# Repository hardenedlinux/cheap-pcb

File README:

## Cheap PCB: Better understanding the current status of hardware supply chain

We did this experimental for fun and profit( better assessment for hardware supply chain security). Read the [full story](https://github.com/hardenedlinux/cheap-pcb/blob/main/cheap-pcb-story.md).

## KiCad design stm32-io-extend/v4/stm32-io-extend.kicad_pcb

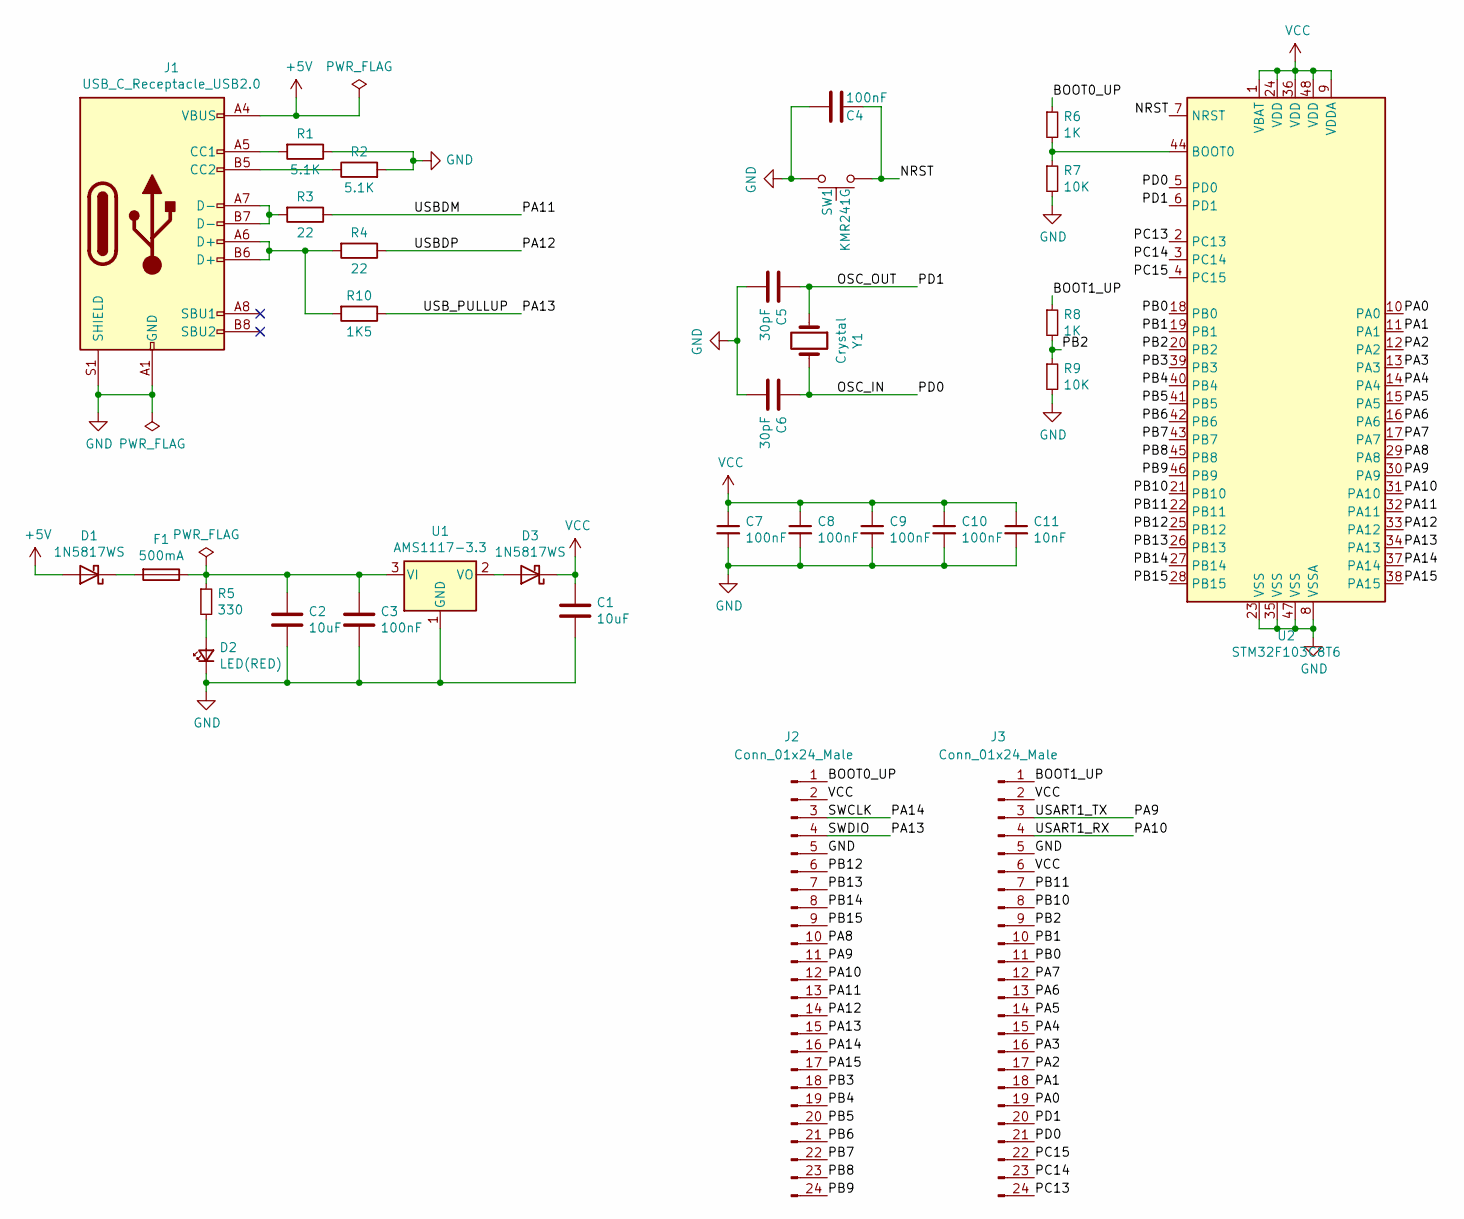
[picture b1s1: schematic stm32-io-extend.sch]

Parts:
C1, C2: 10uF; C_0603_1608Metric_Pad1.08x0.95mm_HandSolder
C3, C4, C7, C8, C9, C10: 100nF; C_0603_1608Metric_Pad1.08x0.95mm_HandSolder
C5, C6: 30pF; C_0603_1608Metric_Pad1.08x0.95mm_HandSolder
C11: 10nF; C_0603_1608Metric_Pad1.08x0.95mm_HandSolder
D1, D3: 1N5817WS; D_SOD-323_HandSoldering
D2: LED(RED); LED_0603_1608Metric_Pad1.05x0.95mm_HandSolder
F1: 500mA; Fuse_0805_2012Metric_Pad1.15x1.40mm_HandSolder
J1: USB_C_Receptacle_USB2.0; USB_C_Receptacle_Palconn_UTC16-G
J2, J3: Conn_01x24_Male; PinHeader_1x24_P2.54mm_Vertical
R1, R2: 5.1K; R_0603_1608Metric_Pad0.98x0.95mm_HandSolder
R3, R4: 22; R_0603_1608Metric_Pad0.98x0.95mm_HandSolder
R5: 330; R_0603_1608Metric_Pad0.98x0.95mm_HandSolder
R6, R8: 1K; R_0603_1608Metric_Pad0.98x0.95mm_HandSolder
R7, R9: 10K; R_0603_1608Metric_Pad0.98x0.95mm_HandSolder
R10: 1K5; R_0603_1608Metric_Pad0.98x0.95mm_HandSolder
SW1: KMR241G; SW_Push_1P1T-SH_NO_CK_KMR2xxG
U1: AMS1117-3.3; SOT-89-3_Handsoldering
U2: STM32F103C8T6; LQFP-48_7x7mm_P0.5mm
Y1: Crystal; Crystal_SMD_HC49-SD_HandSoldering

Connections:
+5V: D1.2 (A), J1.A4 (VBUS), J1.A9 (VBUS), J1.B4 (VBUS), J1.B9 (VBUS)
/BOOT0_UP: J2.1, R6.1
/BOOT1_UP: J3.1, R8.1
/NRST: C4.1, SW1.1, U2.7 (NRST)
/OSC_IN: C6.1, J3.21, U2.5 (PD0), Y1.2
/OSC_OUT: C5.1, J3.20, U2.6 (PD1), Y1.1
/PA0: J3.19, U2.10 (PA0)
/PA1: J3.18, U2.11 (PA1)
/PA2: J3.17, U2.12 (PA2)
/PA3: J3.16, U2.13 (PA3)
/PA4: J3.15, U2.14 (PA4)
/PA5: J3.14, U2.15 (PA5)
/PA6: J3.13, U2.16 (PA6)
/PA7: J3.12, U2.17 (PA7)
/PA8: J2.10, U2.29 (PA8)
/PA9: J2.11, J3.3, U2.30 (PA9)
/PA10: J2.12, J3.4, U2.31 (PA10)
/PA11: J2.13, R3.1, U2.32 (PA11)
/PA12: J2.14, R4.1, U2.33 (PA12)
/PA13: J2.4, J2.15, R10.1, U2.34 (PA13)
/PA14: J2.3, J2.16, U2.37 (PA14)
/PA15: J2.17, U2.38 (PA15)
/PB0: J3.11, U2.18 (PB0)
/PB1: J3.10, U2.19 (PB1)
/PB2: J3.9, R8.2, R9.1, U2.20 (PB2)
/PB3: J2.18, U2.39 (PB3)
/PB4: J2.19, U2.40 (PB4)
/PB5: J2.20, U2.41 (PB5)
/PB6: J2.21, U2.42 (PB6)
/PB7: J2.22, U2.43 (PB7)
/PB8: J2.23, U2.45 (PB8)
/PB9: J2.24, U2.46 (PB9)
/PB10: J3.8, U2.21 (PB10)
/PB11: J3.7, U2.22 (PB11)
/PB12: J2.6, U2.25 (PB12)
/PB13: J2.7, U2.26 (PB13)
/PB14: J2.8, U2.27 (PB14)
/PB15: J2.9, U2.28 (PB15)
/PC13: J3.24, U2.2 (PC13)
/PC14: J3.23, U2.3 (PC14)
/PC15: J3.22, U2.4 (PC15)
GND: C1.2, C2.2, C3.2, C4.2, C5.2, C6.2, C7.2, C8.2, C9.2, C10.2, C11.2, D2.1 (K), J1.A1 (GND), J1.A12 (GND), J1.B1 (GND), J1.B12 (GND), J1.S1 (SHIELD), J2.5, J3.5, R1.1, R2.2, R7.2, R9.2, SW1.2, U1.1 (GND), U2.8 (VSSA), U2.23 (VSS), U2.35 (VSS), U2.47 (VSS)
unnamed: C2.1, C3.1, F1.1, R5.1, U1.3 (VI)
unnamed: D1.1 (K), F1.2
unnamed: D2.2 (A), R5.2
unnamed: D3.2 (A), U1.2 (VO)
unnamed: J1.A5 (CC1), R1.2
unnamed: J1.A6 (D+), J1.B6 (D+), R4.2, R10.2
unnamed: J1.A7 (D-), J1.B7 (D-), R3.2
unnamed: J1.B5 (CC2), R2.1
unnamed: R6.2, R7.1, U2.44 (BOOT0)
VCC: C1.1, C7.1, C8.1, C9.1, C10.1, C11.1, D3.1 (K), J2.2, J3.2, J3.6, U2.1 (VBAT), U2.9 (VDDA), U2.24 (VDD), U2.36 (VDD), U2.48 (VDD)

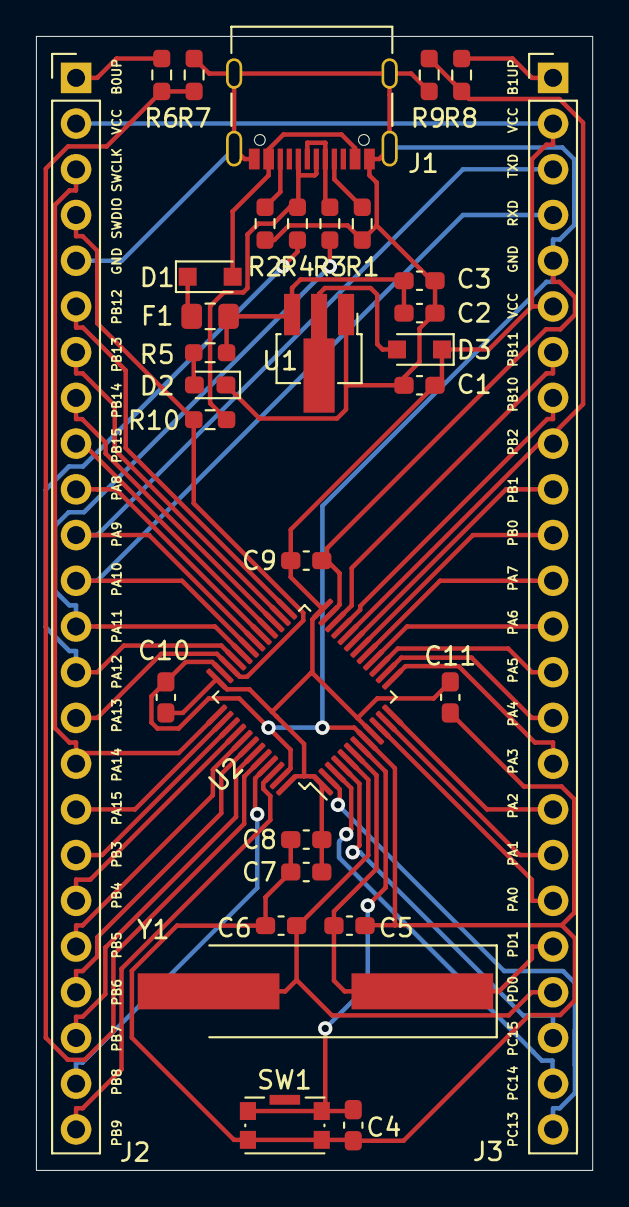
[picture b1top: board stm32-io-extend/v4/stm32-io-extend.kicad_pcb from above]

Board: 2 copper layers, 30.9 x 63.0 mm, 32 parts (0 on the bottom side), 52 nets.

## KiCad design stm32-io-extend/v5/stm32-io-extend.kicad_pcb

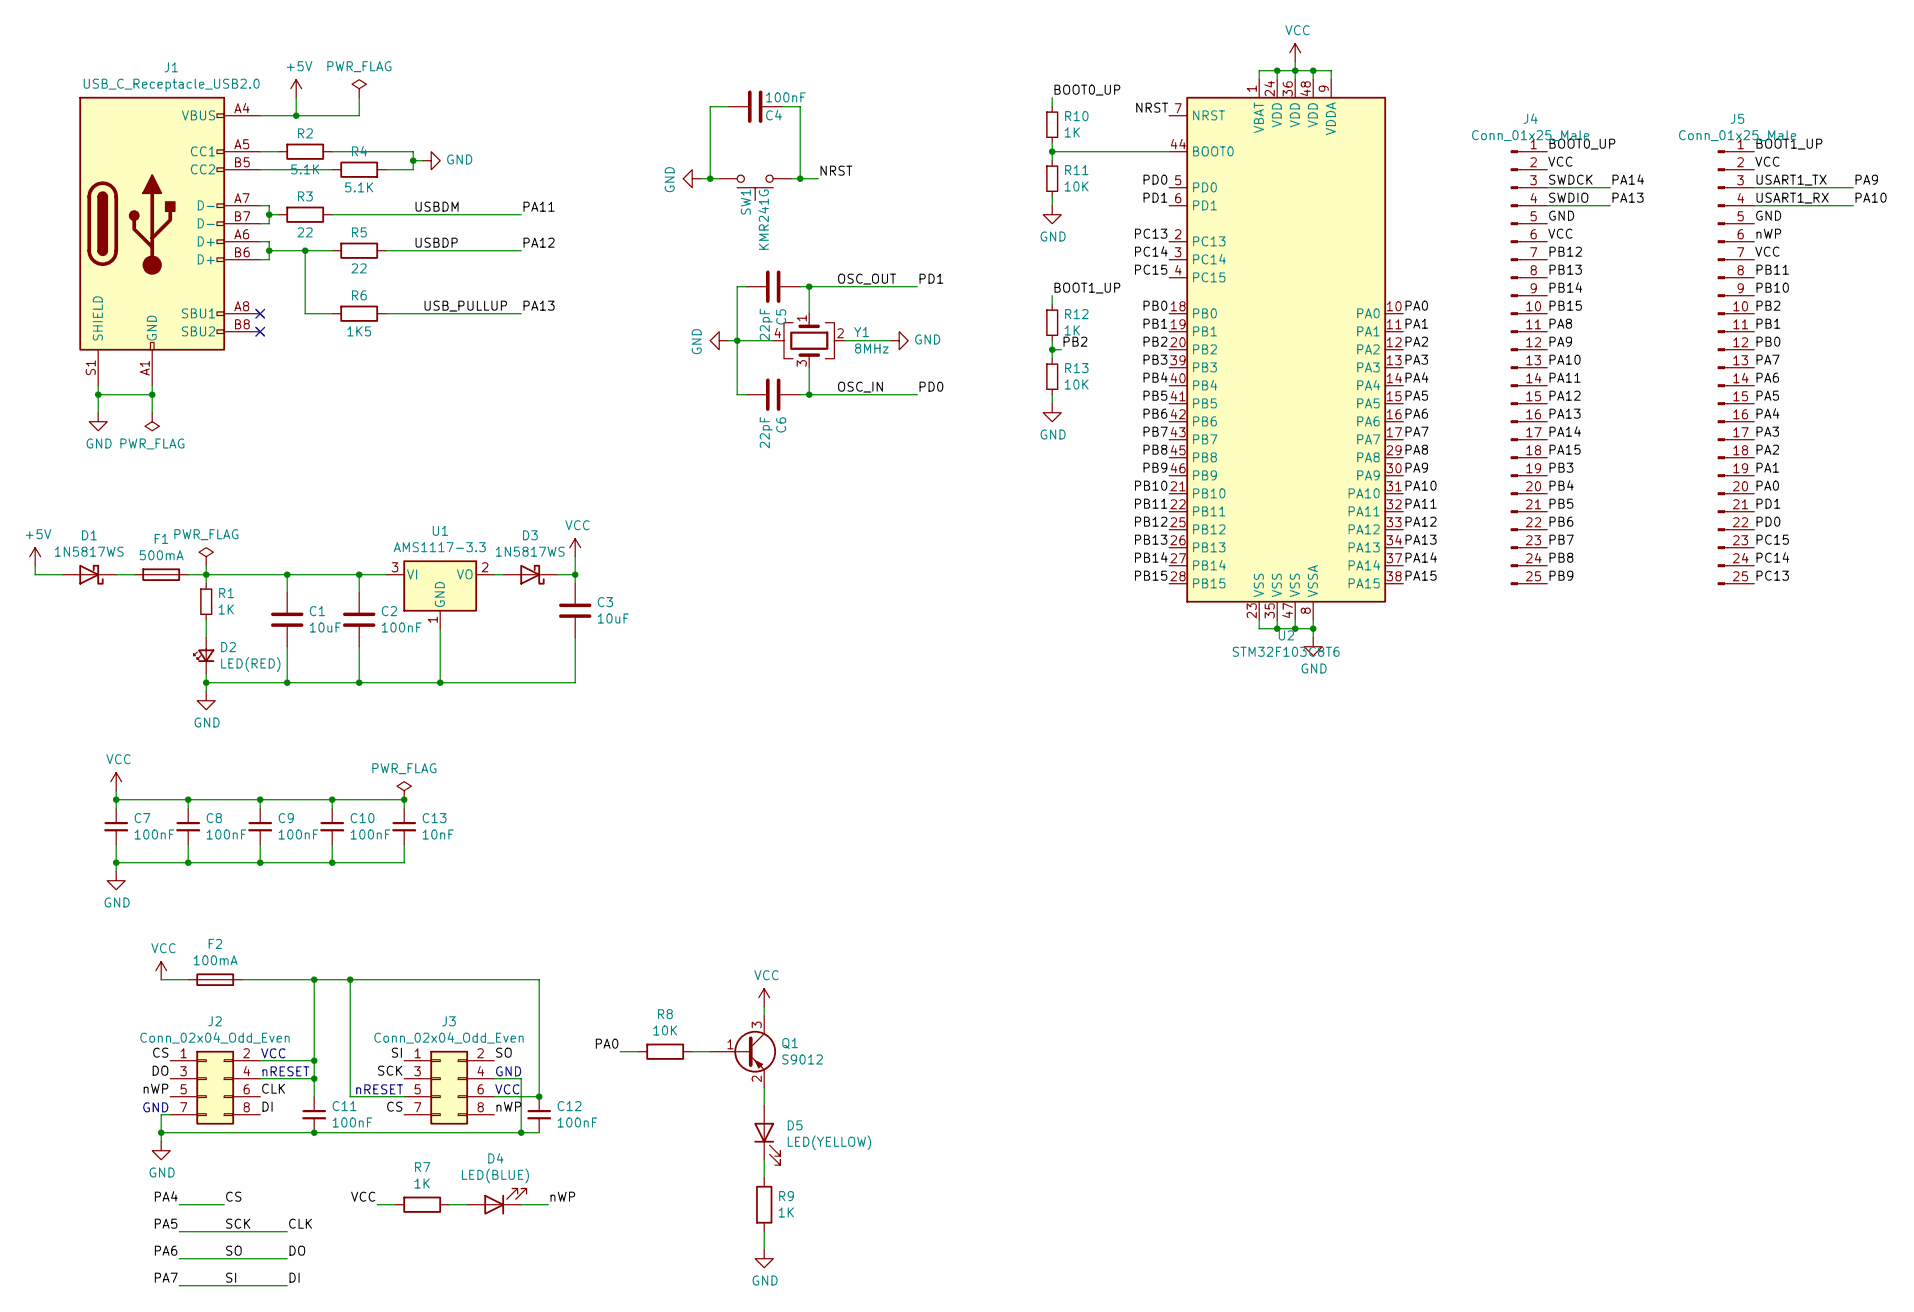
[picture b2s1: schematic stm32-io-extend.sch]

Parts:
C1, C3: 10uF; C_0603_1608Metric_Pad1.08x0.95mm_HandSolder
C2, C4, C7, C8, C9, C10, C11, C12: 100nF; C_0603_1608Metric_Pad1.08x0.95mm_HandSolder
C5, C6: 22pF; C_0603_1608Metric_Pad1.08x0.95mm_HandSolder
C13: 10nF; C_0603_1608Metric_Pad1.08x0.95mm_HandSolder
D1, D3: 1N5817WS; D_SOD-323_HandSoldering
D2: LED(RED); LED_0603_1608Metric_Pad1.05x0.95mm_HandSolder
D4: LED(BLUE); LED_0603_1608Metric_Pad1.05x0.95mm_HandSolder
D5: LED(YELLOW); LED_0603_1608Metric_Pad1.05x0.95mm_HandSolder
F1: 500mA; Fuse_0805_2012Metric_Pad1.15x1.40mm_HandSolder
F2: 100mA; Fuse_0805_2012Metric_Pad1.15x1.40mm_HandSolder
J1: USB_C_Receptacle_USB2.0; USB_C_Receptacle_Palconn_UTC16-G
J2, J3: Conn_02x04_Odd_Even; PinHeader_2x04_P2.54mm_Vertical
J4, J5: Conn_01x25_Male; PinHeader_1x25_P2.54mm_Vertical
Q1: S9012; SOT-23_Handsoldering
R1, R7, R9, R10, R12: 1K; R_0603_1608Metric_Pad0.98x0.95mm_HandSolder
R2, R4: 5.1K; R_0603_1608Metric_Pad0.98x0.95mm_HandSolder
R3, R5: 22; R_0603_1608Metric_Pad0.98x0.95mm_HandSolder
R6: 1K5; R_0603_1608Metric_Pad0.98x0.95mm_HandSolder
R8, R11, R13: 10K; R_0603_1608Metric_Pad0.98x0.95mm_HandSolder
SW1: KMR241G; SW_Push_1P1T-SH_NO_CK_KMR2xxG
U1: AMS1117-3.3; SOT-89-3_Handsoldering
U2: STM32F103C8T6; LQFP-48_7x7mm_P0.5mm
Y1: 8MHz; Crystal_SMD_3225-4Pin_3.2x2.5mm_HandSoldering

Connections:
+5V: D1.2 (A), J1.A4 (VBUS), J1.A9 (VBUS), J1.B4 (VBUS), J1.B9 (VBUS)
/BOOT0_UP: J4.1, R10.1
/BOOT1_UP: J5.1, R12.1
/CLK: J2.6, J3.3, J5.15, U2.15 (PA5)
/CS: J2.1, J3.7, J5.16, U2.14 (PA4)
/DI: J2.8, J3.1, J5.13, U2.17 (PA7)
/DO: J2.3, J3.2, J5.14, U2.16 (PA6)
/NRST: C4.1, SW1.1, U2.7 (NRST)
/OSC_IN: C6.1, J5.22, U2.5 (PD0), Y1.3
/OSC_OUT: C5.1, J5.21, U2.6 (PD1), Y1.1
/PA0: J5.20, R8.2, U2.10 (PA0)
/PA1: J5.19, U2.11 (PA1)
/PA2: J5.18, U2.12 (PA2)
/PA3: J5.17, U2.13 (PA3)
/PA8: J4.11, U2.29 (PA8)
/PA9: J4.12, J5.3, U2.30 (PA9)
/PA10: J4.13, J5.4, U2.31 (PA10)
/PA11: J4.14, R3.1, U2.32 (PA11)
/PA12: J4.15, R5.1, U2.33 (PA12)
/PA13: J4.4, J4.16, R6.1, U2.34 (PA13)
/PA14: J4.3, J4.17, U2.37 (PA14)
/PA15: J4.18, U2.38 (PA15)
/PB0: J5.12, U2.18 (PB0)
/PB1: J5.11, U2.19 (PB1)
/PB2: J5.10, R12.2, R13.1, U2.20 (PB2)
/PB3: J4.19, U2.39 (PB3)
/PB4: J4.20, U2.40 (PB4)
/PB5: J4.21, U2.41 (PB5)
/PB6: J4.22, U2.42 (PB6)
/PB7: J4.23, U2.43 (PB7)
/PB8: J4.24, U2.45 (PB8)
/PB9: J4.25, U2.46 (PB9)
/PB10: J5.9, U2.21 (PB10)
/PB11: J5.8, U2.22 (PB11)
/PB12: J4.7, U2.25 (PB12)
/PB13: J4.8, U2.26 (PB13)
/PB14: J4.9, U2.27 (PB14)
/PB15: J4.10, U2.28 (PB15)
/PC13: J5.25, U2.2 (PC13)
/PC14: J5.24, U2.3 (PC14)
/PC15: J5.23, U2.4 (PC15)
/nWP: D4.1 (K), J2.5, J3.8, J5.6
GND: C1.2, C2.2, C3.2, C4.2, C5.2, C6.2, C7.2, C8.2, C9.2, C10.2, C11.2, C12.2, C13.2, D2.1 (K), J1.A1 (GND), J1.A12 (GND), J1.B1 (GND), J1.B12 (GND), J1.S1 (SHIELD), J2.7, J3.4, J4.5, J5.5, R2.1, R4.2, R9.2, R11.2, R13.2, SW1.2, U1.1 (GND), U2.8 (VSSA), U2.23 (VSS), U2.35 (VSS), U2.47 (VSS), Y1.2, Y1.4
unnamed: C1.1, C2.1, F1.1, R1.1, U1.3 (VI)
unnamed: C11.1, C12.1, F2.2, J2.2, J2.4, J3.5, J3.6
unnamed: D1.1 (K), F1.2
unnamed: D2.2 (A), R1.2
unnamed: D3.2 (A), U1.2 (VO)
unnamed: D4.2 (A), R7.1
unnamed: D5.1 (K), R9.1
unnamed: D5.2 (A), Q1.2 (E)
unnamed: J1.A5 (CC1), R2.2
unnamed: J1.A6 (D+), J1.B6 (D+), R5.2, R6.2
unnamed: J1.A7 (D-), J1.B7 (D-), R3.2
unnamed: J1.B5 (CC2), R4.1
unnamed: Q1.1 (B), R8.1
unnamed: R10.2, R11.1, U2.44 (BOOT0)
VCC: C3.1, C7.1, C8.1, C9.1, C10.1, C13.1, D3.1 (K), F2.1, J4.2, J4.6, J5.2, J5.7, Q1.3 (C), R7.2, U2.1 (VBAT), U2.9 (VDDA), U2.24 (VDD), U2.36 (VDD), U2.48 (VDD)

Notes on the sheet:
VCC
nRESET
GND

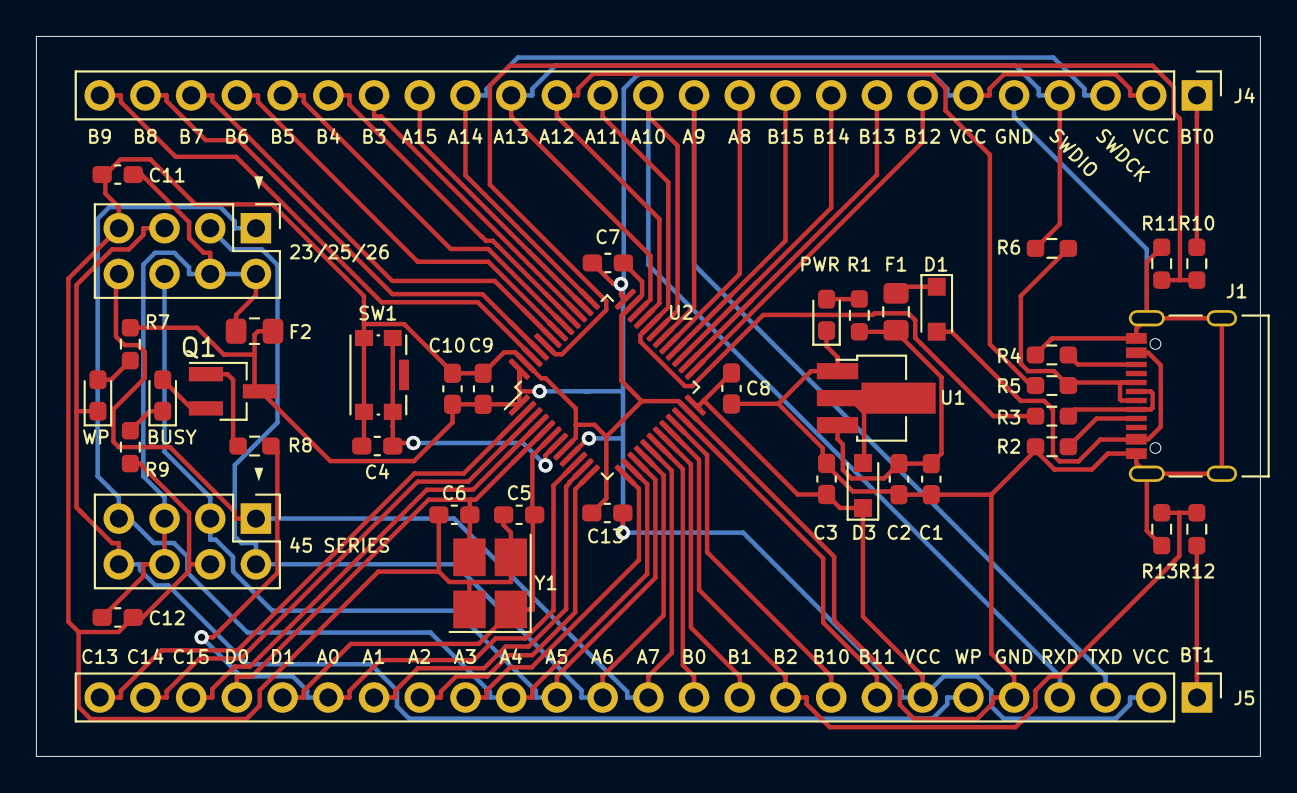
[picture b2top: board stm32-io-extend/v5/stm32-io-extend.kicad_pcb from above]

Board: 2 copper layers, 68.0 x 40.0 mm, 43 parts (0 on the bottom side), 58 nets.

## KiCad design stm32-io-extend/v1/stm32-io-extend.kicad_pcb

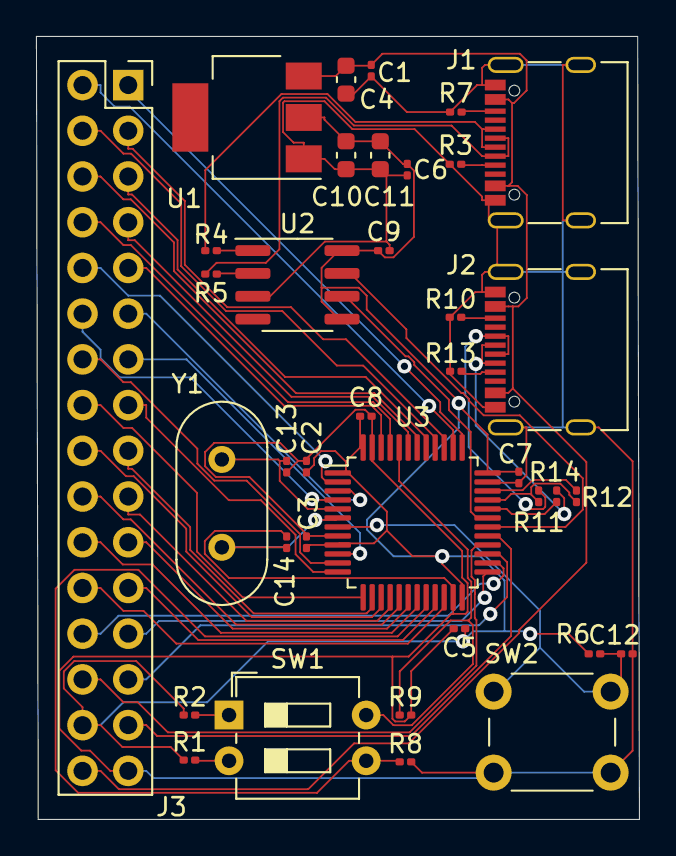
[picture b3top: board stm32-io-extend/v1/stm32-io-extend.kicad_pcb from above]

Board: 2 copper layers, 33.5 x 43.5 mm, 37 parts (0 on the bottom side), 54 nets.

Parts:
C1, C2, C5, C7, C8, C9, C12: 100nF; C_0201_0603Metric
C3: 10nF; C_0201_0603Metric
C4, C10: 10uF; C_0603_1608Metric
C6: 1uF; C_0201_0603Metric
C11: 4.7uF; C_0603_1608Metric
C13, C14: 22pF; C_0201_0603Metric
J1, J2: USB_C_Receptacle_USB2.0; USB_C_Receptacle_Palconn_UTC16-G
J3: Conn_02x16_Odd_Even; PinSocket_2x16_P2.54mm_Vertical
R1, R2: 1K; R_0201_0603Metric
R3, R7, R10, R13: 5K1; R_0201_0603Metric
R4, R5, R11, R14: 22; R_0201_0603Metric
R6, R8, R9: 10K; R_0201_0603Metric
R12: 1K5; R_0201_0603Metric
SW1: SW_DIP_x02; SW_DIP_SPSTx02_Slide_6.7x6.64mm_W7.62mm_P2.54mm_LowProfile
SW2: SW_Push; SW_PUSH_6mm
U1: AMS1117-3.3; SOT-223
U2: CH330N; SOIC-8_3.9x4.9mm_P1.27mm
U3: STM32F103C8Tx; LQFP-48_7x7mm_P0.5mm
Y1: 8MHz; Crystal_HC49-U_Vertical

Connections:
+3V3: C2.1, C3.1, C5.1, C6.1, C7.1, C8.1, C9.1, C10.1, C11.1, J3.30, R1.1, R2.2, R6.1, U1.2, U2.5, U2.8, U3.1, U3.9, U3.24, U3.36, U3.48
+5V: C1.1, C4.1, J1.A4, J1.A9, J1.B4, J1.B9, J2.A4, J2.A9, J2.B4, J2.B9, J3.32, U1.3
/BOOT0: R9.2, SW1.4, U3.44
/BOOT1: R8.2, SW1.3, U3.20
/NRST: C12.1, R6.2, SW2.1, U3.7
/P1: J3.1, U3.37
/P2: J3.2, U3.38
/P3: J3.3, U3.39
/P4: J3.4, U3.40
/P5: J3.5, U3.41
/P6: J3.6, U3.42
/P7: J3.7, U3.43
/P8: J3.8, U3.45
/P9: J3.9, U3.46
/P10: J3.10, U3.2
/P11: J3.11, U3.3
/P12: J3.12, U3.4
/P13: J3.13, U3.10
/P14: J3.14, U3.11
/P15: J3.15, U3.12
/P16: J3.16, U3.13
/P17: J3.17, U3.14
/P18: J3.18, U3.15
/P19: J3.19, U3.16
/P20: J3.20, U3.17
/P21: J3.21, U3.18
/P22: J3.22, U3.19
/P23: J3.23, U3.21
/P24: J3.24, U3.22
/P25: J3.25, U3.25
/P26: J3.26, U3.26
/P27: J3.27, U3.27
/P28: J3.28, U3.28
/P29: J3.29, U3.29
/USART1_RX: U2.6, U3.31
/USART1_TX: U2.7, U3.30
/USBDM: R14.1, U3.32
/USBDP: R11.1, R12.1, U3.33
/USB_PULLUP: R12.2, U3.34
GND: C1.2, C2.2, C3.2, C4.2, C5.2, C6.2, C7.2, C8.2, C9.2, C10.2, C11.2, C12.2, C13.2, C14.2, J1.A1, J1.A12, J1.B1, J1.B12, J1.S1, J2.A1, J2.A12, J2.B1, J2.B12, J2.S1, J3.31, R3.1, R7.1, R8.1, R9.1, R10.1, R13.1, SW2.2, U1.1, U2.3, U3.8, U3.23, U3.35, U3.47
unnamed: C13.1, U3.5, Y1.1
unnamed: C14.1, U3.6, Y1.2
unnamed: J1.A5, R3.2
unnamed: J1.A6, J1.B6, R4.2
unnamed: J1.A7, J1.B7, R5.2
unnamed: J1.B5, R7.2
unnamed: J2.A5, R13.2
unnamed: J2.A6, J2.B6, R11.2
unnamed: J2.A7, J2.B7, R14.2
unnamed: J2.B5, R10.2
unnamed: R1.2, SW1.2
unnamed: R2.1, SW1.1
unnamed: R4.1, U2.1
unnamed: R5.1, U2.2

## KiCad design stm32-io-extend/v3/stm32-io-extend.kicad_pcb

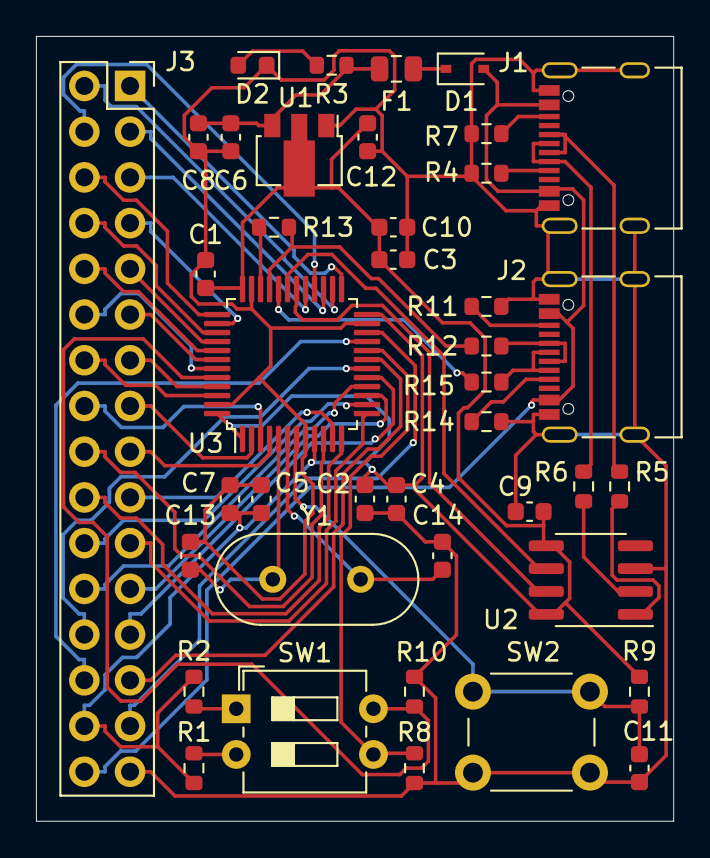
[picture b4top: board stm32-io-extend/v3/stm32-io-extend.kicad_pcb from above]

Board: 2 copper layers, 35.4 x 43.6 mm, 41 parts (0 on the bottom side), 57 nets.

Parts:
C1, C3, C5, C7, C8, C9, C11: 100nF; C_0603_1608Metric
C2: 10nF; C_0603_1608Metric
C4: 1uF; C_0603_1608Metric
C6, C12: 10uF; C_0603_1608Metric
C10: 4.7uF; C_0603_1608Metric
C13, C14: 22pF; C_0603_1608Metric
D1: 1N5817WS; D_SOD-323
D2: LED (RED); LED_0603_1608Metric
F1: 500mA; Fuse_0805_2012Metric
J1, J2: USB_C_Receptacle_USB2.0; USB_C_Receptacle_Palconn_UTC16-G
J3: Conn_02x16_Odd_Even; PinSocket_2x16_P2.54mm_Vertical
R1, R2: 1K; R_0603_1608Metric
R3: 330; R_0603_1608Metric
R4, R7, R11, R14: 5K1; R_0603_1608Metric
R5, R6, R12, R15: 22; R_0603_1608Metric
R8, R9, R10: 10K; R_0603_1608Metric
R13: 1K5; R_0603_1608Metric
SW1: SW_DIP_x02; SW_DIP_SPSTx02_Slide_6.7x6.64mm_W7.62mm_P2.54mm_LowProfile
SW2: SW_Push; SW_PUSH_6mm
U1: AMS1117-3.3; SOT-89-3
U2: CH330N; SOIC-8_3.9x4.9mm_P1.27mm
U3: STM32F103C8T6; LQFP-48_7x7mm_P0.5mm
Y1: 8MHz; Crystal_HC49-U_Vertical

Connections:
+3V3: C1.1, C2.1, C3.1, C4.1, C5.1, C7.1, C9.1, C10.1, C12.1, J3.30, R1.1, R2.2, R9.1, U1.2, U2.5, U2.8, U3.1, U3.9, U3.24, U3.36, U3.48
+5V: D1.2, J1.A4, J1.A9, J1.B4, J1.B9, J2.A4, J2.A9, J2.B4, J2.B9, J3.32
/BOOT0: R10.2, SW1.4, U3.44
/BOOT1: R8.2, SW1.3, U3.20
/NRST: C11.1, R9.2, SW2.1, U3.7
/P1: J3.1, U3.25
/P2: J3.2, U3.26
/P3: J3.3, U3.27
/P4: J3.4, U3.28
/P5: J3.5, U3.29
/P6: J3.6, U3.37
/P7: J3.7, U3.38
/P8: J3.8, U3.39
/P9: J3.9, U3.40
/P10: J3.10, U3.41
/P11: J3.11, U3.42
/P12: J3.12, U3.43
/P13: J3.13, U3.45
/P14: J3.14, U3.46
/P15: J3.15, U3.2
/P16: J3.16, U3.3
/P17: J3.17, U3.4
/P18: J3.18, U3.10
/P19: J3.19, U3.11
/P20: J3.20, U3.12
/P21: J3.21, U3.13
/P22: J3.22, U3.14
/P23: J3.23, U3.15
/P24: J3.24, U3.16
/P25: J3.25, U3.17
/P26: J3.26, U3.18
/P27: J3.27, U3.19
/P28: J3.28, U3.21
/P29: J3.29, U3.22
/USART1_RX: U2.6, U3.31
/USART1_TX: U2.7, U3.30
/USBDM: R15.1, U3.32
/USBDP: R12.1, R13.1, U3.33
/USB_PULLUP: R13.2, U3.34
GND: C1.2, C2.2, C3.2, C4.2, C5.2, C6.2, C7.2, C8.2, C9.2, C10.2, C11.2, C12.2, C13.2, C14.2, D2.1, J1.A1, J1.A12, J1.B1, J1.B12, J1.S1, J2.A1, J2.A12, J2.B1, J2.B12, J2.S1, J3.31, R4.1, R7.1, R8.1, R10.1, R11.1, R14.1, SW2.2, U1.1, U2.3, U3.8, U3.23, U3.35, U3.47
unnamed: C6.1, C8.1, F1.1, R3.1, U1.3
unnamed: C13.1, U3.5, Y1.1
unnamed: C14.1, U3.6, Y1.2
unnamed: D1.1, F1.2
unnamed: D2.2, R3.2
unnamed: J1.A5, R4.2
unnamed: J1.A6, J1.B6, R5.2
unnamed: J1.A7, J1.B7, R6.2
unnamed: J1.B5, R7.2
unnamed: J2.A5, R14.2
unnamed: J2.A6, J2.B6, R12.2
unnamed: J2.A7, J2.B7, R15.2
unnamed: J2.B5, R11.2
unnamed: R1.2, SW1.2
unnamed: R2.1, SW1.1
unnamed: R5.1, U2.1
unnamed: R6.1, U2.2

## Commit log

2021-02-10 Hacking Cheap PCB for fun and profit( Yet! another random assessment for hardware supply chain security)
2021-02-19 Fix #1
    Fix typos
